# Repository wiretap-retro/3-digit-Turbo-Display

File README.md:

# 3-digit Turbo Display
A 3-digit turbo display for retro PC's.

\

## Info
This is a 3-digit turbo display for retro PC's. I modeled the size after one out of a case I own, so it is a standard size. It functions in the same way as my 2-digit turbo display. The design utilizes an ATTiny85 and MAX7219 chip for digit display.

## Code
No code exists yet, however the turbo.ino file from my 2-digit display can be copied, and then add the Arduino compatible MAX7219 library.

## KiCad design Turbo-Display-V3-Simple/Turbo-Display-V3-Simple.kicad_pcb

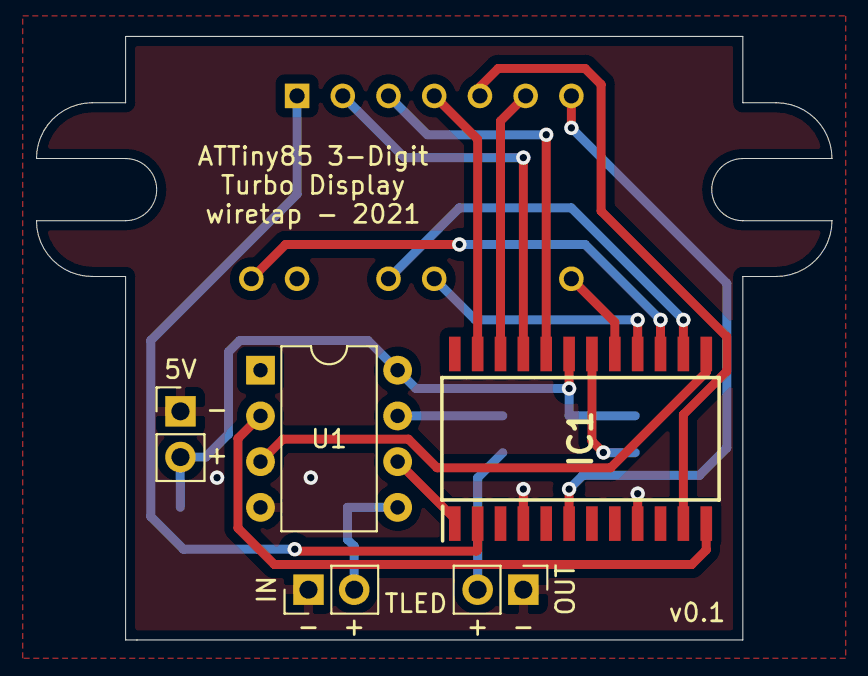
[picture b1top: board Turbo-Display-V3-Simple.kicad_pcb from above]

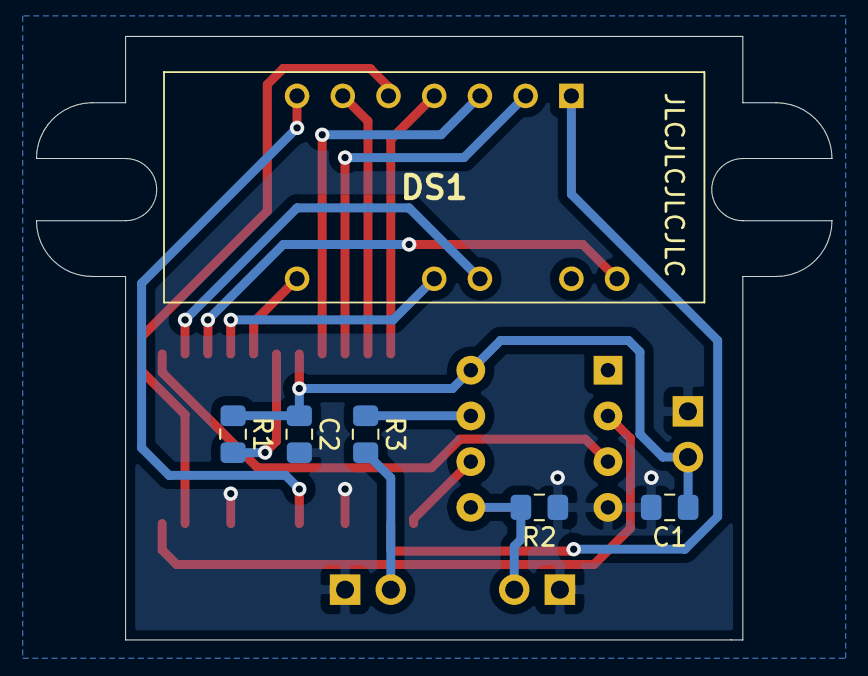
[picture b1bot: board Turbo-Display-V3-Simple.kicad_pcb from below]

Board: 2 copper layers, 44.2 x 33.5 mm, 11 parts (6 on the bottom side), 20 nets.

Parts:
5V: +5V; PinHeader_1x02_P2.54mm_Vertical
C1, C2: 0.1uF; C_0805_2012Metric_Pad1.15x1.40mm_HandSolder
DS1: HDSP-433G; HDSP433G
IC1: MAX7219EWG+; SOIC127P1032X265-24N
IN: TLED_IN; PinHeader_1x02_P2.54mm_Vertical
OUT: TLED_OUT; PinHeader_1x02_P2.54mm_Vertical
R1: 28k; R_0805_2012Metric_Pad1.15x1.40mm_HandSolder
R2: 10k; R_0805_2012Metric_Pad1.15x1.40mm_HandSolder
R3: 330; R_0805_2012Metric_Pad1.15x1.40mm_HandSolder
U1: ATtiny85-20PU; DIP-8_W7.62mm

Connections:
+5V: 5V.2, C1.1, C2.1, IC1.19, R1.1, U1.8
/CLOCK: IC1.13, U1.3
/DATA: IC1.1, U1.6
/DIG1: DS1.1, IC1.2
/DIG2: DS1.5, IC1.11
/DIG3: DS1.7, IC1.6
/LOAD: IC1.12, U1.2
/SEGA: DS1.12, IC1.14
/SEGB: DS1.11, IC1.16
/SEGC: DS1.3, IC1.20
/SEGD: DS1.4, IC1.23
/SEGDP: DS1.6, IC1.22
/SEGE: DS1.2, IC1.21
/SEGF: DS1.15, IC1.15
/SEGG: DS1.8, IC1.17
/TLED_IN: IN.2, R2.1, U1.5
/TLED_OUT: R3.2, U1.7
GND: 5V.1, C1.2, C2.2, IC1.4, IC1.9, IN.1, OUT.1, R2.2, U1.4
unnamed: IC1.18, R1.2
unnamed: OUT.2, R3.1
